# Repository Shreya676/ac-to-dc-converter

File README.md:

# AC to DC Converter Circuit (5V Output)

This project demonstrates a simple AC to DC converter circuit using a bridge rectifier and a 7805 voltage regulator. The output is a regulated 5V DC, suitable for powering microcontrollers or other 5V logic circuits.

---

## 🧰 Components Used

| Component | Description             |
|-----------|-------------------------|
| D1, D3, D4, D5 | 1N4007 Diodes (Bridge Rectifier) |
| C1        | Electrolytic Capacitor (for filtering) |
| U1        | 7805 Voltage Regulator (5V output) |
| R1        | Current Limiting Resistor for LED |
| D2        | LED (Power indicator) |
| J1        | 2-pin Connector (AC Input) |
| PWR_FLAG  | Power flag (used in PCB design software) |

---

## ⚙️ Working Principle

1. **AC Input**: The AC voltage is applied at the connector `J1` (Input1 and Input2).
2. **Bridge Rectifier**: Diodes D1, D3, D4, and D5 form a bridge rectifier to convert the AC voltage to pulsating DC.
3. **Smoothing**: Capacitor C1 filters the pulsating DC and provides a smoother DC output.
4. **Voltage Regulation**: The 7805 IC (U1) regulates the voltage to a constant 5V DC.
5. **Power Indication**: LED D2 lights up when the 5V output is active. R1 limits the current to the LED.

---

## 🔌 Output

- **DC Output Voltage**: 5V (regulated)
- **Usable For**: Powering 5V devices like Arduino, sensors, or microcontrollers.

---

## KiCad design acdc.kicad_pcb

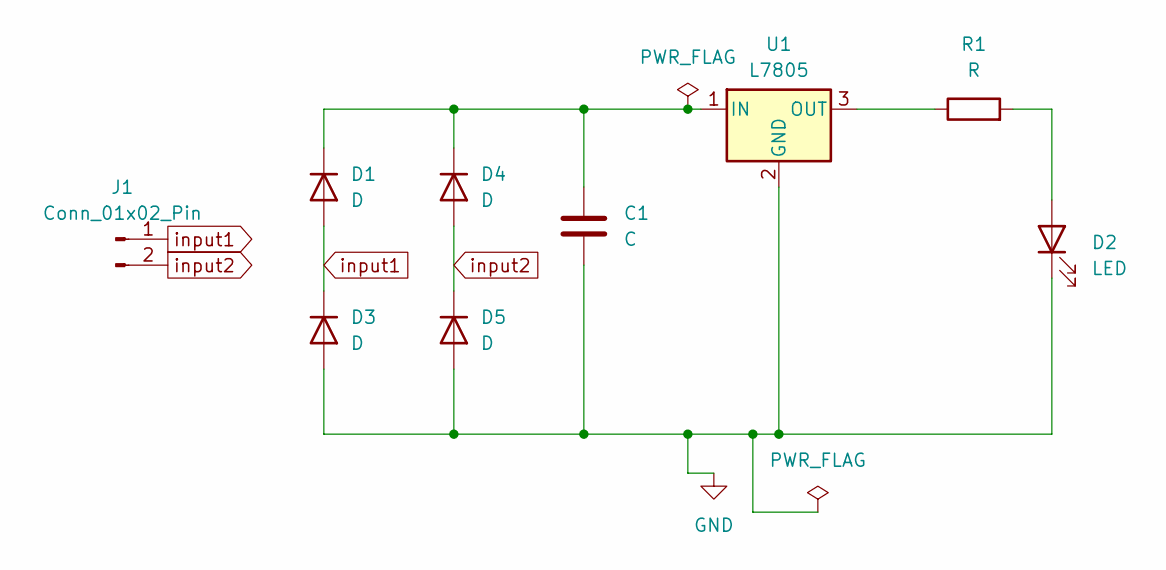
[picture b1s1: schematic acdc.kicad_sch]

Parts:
C1: C; C_Radial_D6.3mm_H11.0mm_P2.50mm
D1, D3, D4, D5: D; D_5W_P10.16mm_Horizontal
D2: LED; LED_D5.0mm
J1: Conn_01x02_Pin; JWT_A3963_1x02_P3.96mm_Vertical
R1: R; R_Axial_DIN0207_L6.3mm_D2.5mm_P15.24mm_Horizontal
U1: L7805; TO-220-3_Vertical

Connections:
GND: C1.2, D2.1 (K), D3.2 (A), D5.2 (A), U1.2 (GND)
unnamed: C1.1, D1.1 (K), D4.1 (K), U1.1 (IN)
unnamed: D2.2 (A), R1.2
unnamed: R1.1, U1.3 (OUT)
input1: D1.2 (A), D3.1 (K), J1.1
input2: D4.2 (A), D5.1 (K), J1.2

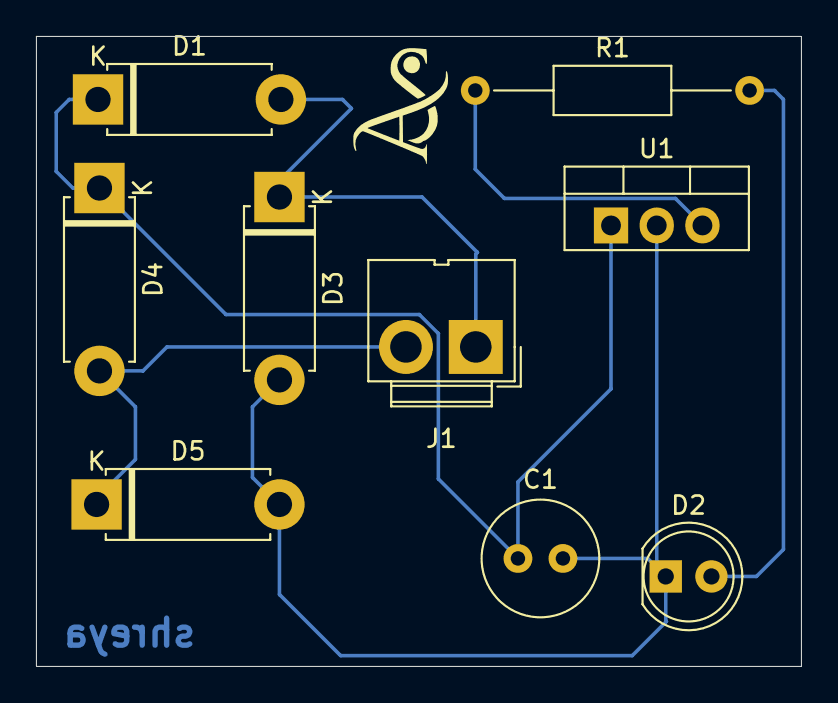
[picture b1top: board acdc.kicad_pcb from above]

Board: 2 copper layers, 42.5 x 35.0 mm, 9 parts (0 on the bottom side), 6 nets.

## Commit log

2025-04-30 initial setup
2025-04-30 ac to dc converter circuit
2025-04-30 added pcb design
2025-04-30 actodc
